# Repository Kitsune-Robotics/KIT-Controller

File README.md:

# KIT-Controller

Hardware for the KIT Controller

Migrated from https://kitsunehosting.net/gitea/Kenwood/lewis-crawler

# Getting Started

## Clone this repo

```shell
git clone https://github.com/Kitsune-Robotics/KIT-Controller.git --recurse-submodules
```

You will *need* the submodules as all of the boards in `Hardware` have several library dependencies.

`Hardware/BackPlane` Contains the backplane for the system, the backplane connects all other cards together.
`Hardware/KIT_Controller` Is the main processing unit of the system, the core computer where this code (will eventually) live
`Hardware/Dev_Card` Is a development tool, made to be slotted into any slot and connected via probes, solder jumpers and wires to aid in developing/debugging

You can re-initalize/update submodules by using the command

```shell
git submodule update --init --recursive
```

## 3D Models

Some libraries (namely my own `kenwoodfox-kicad-libraries` lib) requires setting a path variable to show some 3d models.

Follow the instructions inside of these libraries folders for how to set these paths.

# Parts

The kit controller and its other boards use the Sullins [EBM15DSEH](https://www.digikey.com/en/products/detail/sullins-connector-solutions/EBM15DSEH/927297) to connect to the backplane.

Its a little expensive, in the future the [WingTAT ED30MEBGFBK ](https://www.lcsc.com/product-detail/Card-Edge-Connectors_WingTAT-ED30MEBGFBK_C5242012.html) is a possible replacement.

## Project Layout

If you want to use this project template for yourself, you can find it [here!](https://github.com/KenwoodFox/Project-Template)

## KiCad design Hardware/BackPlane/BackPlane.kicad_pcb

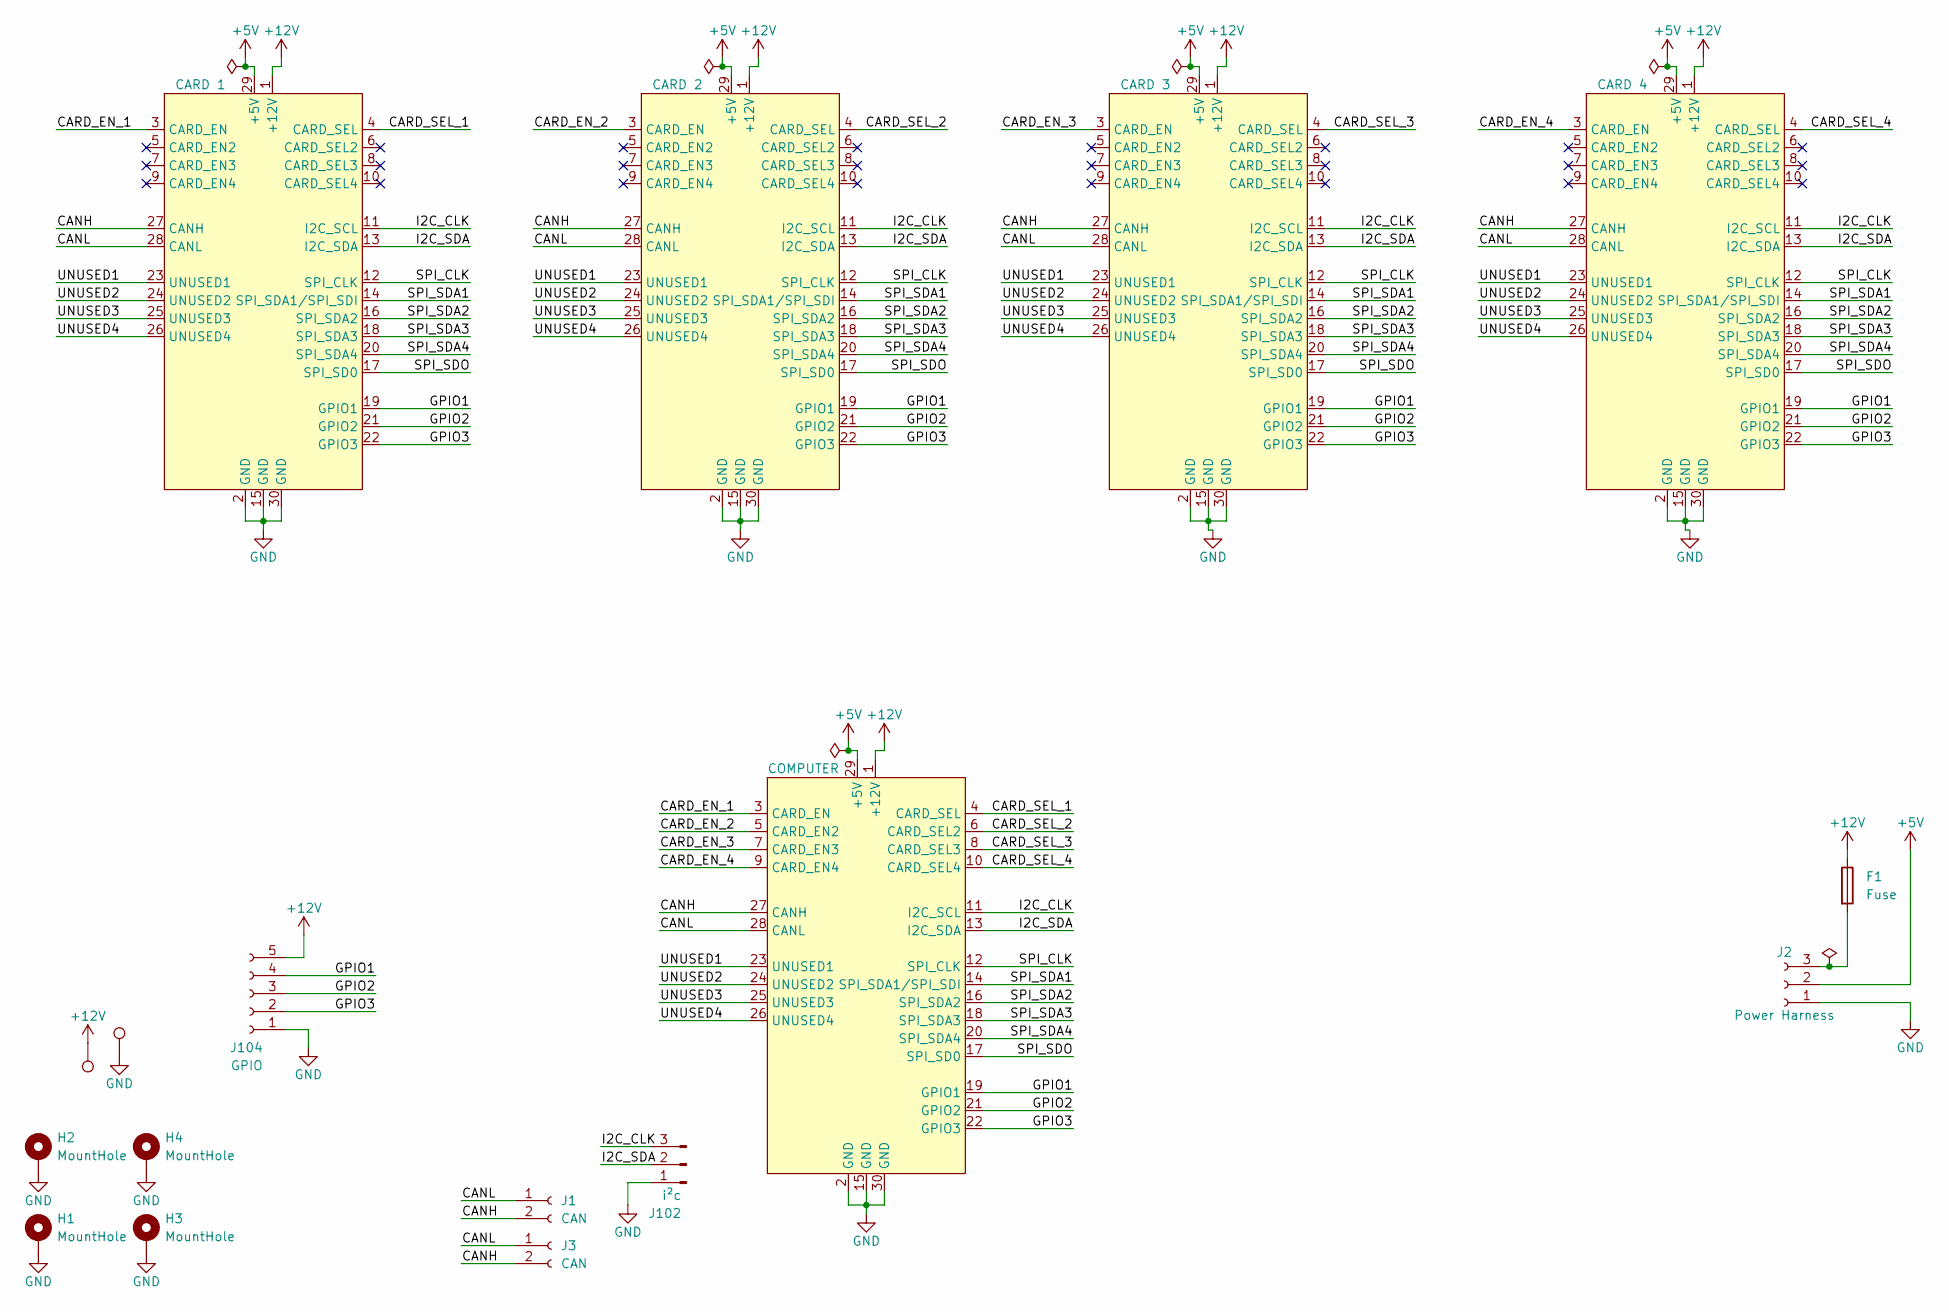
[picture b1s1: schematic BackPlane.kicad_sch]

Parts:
F1: Fuse; Fuseholder_Littelfuse_100_series_5x20mm; LCSC# C3130
H1, H2, H3, H4: MountHole; MountingHole_3.5mm_Pad
J1, J3: CAN; SolderWire-0.5sqmm_1x02_P4.6mm_D0.9mm_OD2.1mm_Relief
J2: Power Harness; SolderWire-0.25sqmm_1x03_P4.5mm_D0.65mm_OD2mm_Relief
J102: i²c; SolderWire-0.25sqmm_1x03_P4.5mm_D0.65mm_OD2mm_Relief
J104: GPIO; SolderWire-0.5sqmm_1x05_P4.6mm_D0.9mm_OD2.1mm_Relief
TP101, TP102: TestPoint; TestPoint_Loop_D2.54mm_Drill1.5mm_Beaded
U101: COMPUTER; EBM15DSEH
U102: CARD 1; EBM15DSEH
U103: CARD 2; EBM15DSEH
U104: CARD 3; EBM15DSEH
U105: CARD 4; EBM15DSEH

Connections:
+5V: J2.2, U101.29 (+5V), U102.29 (+5V), U103.29 (+5V), U104.29 (+5V), U105.29 (+5V)
+12V: F1.1, J104.5, TP101.1, U101.1 (+12V), U102.1 (+12V), U103.1 (+12V), U104.1 (+12V), U105.1 (+12V)
/CANH: J1.2, J3.2, U101.27 (CANH), U102.27 (CANH), U103.27 (CANH), U104.27 (CANH), U105.27 (CANH)
/CANL: J1.1, J3.1, U101.28 (CANL), U102.28 (CANL), U103.28 (CANL), U104.28 (CANL), U105.28 (CANL)
/CARD_EN_1: U101.3 (CARD_EN), U102.3 (CARD_EN)
/CARD_EN_2: U101.5 (CARD_EN2), U103.3 (CARD_EN)
/CARD_EN_3: U101.7 (CARD_EN3), U104.3 (CARD_EN)
/CARD_EN_4: U101.9 (CARD_EN4), U105.3 (CARD_EN)
/CARD_SEL_1: U101.4 (CARD_SEL), U102.4 (CARD_SEL)
/CARD_SEL_2: U101.6 (CARD_SEL2), U103.4 (CARD_SEL)
/CARD_SEL_3: U101.8 (CARD_SEL3), U104.4 (CARD_SEL)
/CARD_SEL_4: U101.10 (CARD_SEL4), U105.4 (CARD_SEL)
/GPIO1: J104.4, U101.19 (GPIO1), U102.19 (GPIO1), U103.19 (GPIO1), U104.19 (GPIO1), U105.19 (GPIO1)
/GPIO2: J104.3, U101.21 (GPIO2), U102.21 (GPIO2), U103.21 (GPIO2), U104.21 (GPIO2), U105.21 (GPIO2)
/GPIO3: J104.2, U101.22 (GPIO3), U102.22 (GPIO3), U103.22 (GPIO3), U104.22 (GPIO3), U105.22 (GPIO3)
/I2C_CLK: J102.3, U101.11 (I2C_SCL), U102.11 (I2C_SCL), U103.11 (I2C_SCL), U104.11 (I2C_SCL), U105.11 (I2C_SCL)
/I2C_SDA: J102.2, U101.13 (I2C_SDA), U102.13 (I2C_SDA), U103.13 (I2C_SDA), U104.13 (I2C_SDA), U105.13 (I2C_SDA)
/SPI_CLK: U101.12 (SPI_CLK), U102.12 (SPI_CLK), U103.12 (SPI_CLK), U104.12 (SPI_CLK), U105.12 (SPI_CLK)
/SPI_SDA1: U101.14 (SPI_SDA1/SPI_SDI), U102.14 (SPI_SDA1/SPI_SDI), U103.14 (SPI_SDA1/SPI_SDI), U104.14 (SPI_SDA1/SPI_SDI), U105.14 (SPI_SDA1/SPI_SDI)
/SPI_SDA2: U101.16 (SPI_SDA2), U102.16 (SPI_SDA2), U103.16 (SPI_SDA2), U104.16 (SPI_SDA2), U105.16 (SPI_SDA2)
/SPI_SDA3: U101.18 (SPI_SDA3), U102.18 (SPI_SDA3), U103.18 (SPI_SDA3), U104.18 (SPI_SDA3), U105.18 (SPI_SDA3)
/SPI_SDA4: U101.20 (SPI_SDA4), U102.20 (SPI_SDA4), U103.20 (SPI_SDA4), U104.20 (SPI_SDA4), U105.20 (SPI_SDA4)
/SPI_SDO: U101.17 (SPI_SD0), U102.17 (SPI_SD0), U103.17 (SPI_SD0), U104.17 (SPI_SD0), U105.17 (SPI_SD0)
/UNUSED1: U101.23 (UNUSED1), U102.23 (UNUSED1), U103.23 (UNUSED1), U104.23 (UNUSED1), U105.23 (UNUSED1)
/UNUSED2: U101.24 (UNUSED2), U102.24 (UNUSED2), U103.24 (UNUSED2), U104.24 (UNUSED2), U105.24 (UNUSED2)
/UNUSED3: U101.25 (UNUSED3), U102.25 (UNUSED3), U103.25 (UNUSED3), U104.25 (UNUSED3), U105.25 (UNUSED3)
/UNUSED4: U101.26 (UNUSED4), U102.26 (UNUSED4), U103.26 (UNUSED4), U104.26 (UNUSED4), U105.26 (UNUSED4)
GND: H1.1, H2.1, H3.1, H4.1, J2.1, J102.1, J104.1, TP102.1, U101.2 (GND), U101.15 (GND), U101.30 (GND), U102.2 (GND), U102.15 (GND), U102.30 (GND), U103.2 (GND), U103.15 (GND), U103.30 (GND), U104.2 (GND), U104.15 (GND), U104.30 (GND), U105.2 (GND), U105.15 (GND), U105.30 (GND)
unnamed: F1.2, J2.3

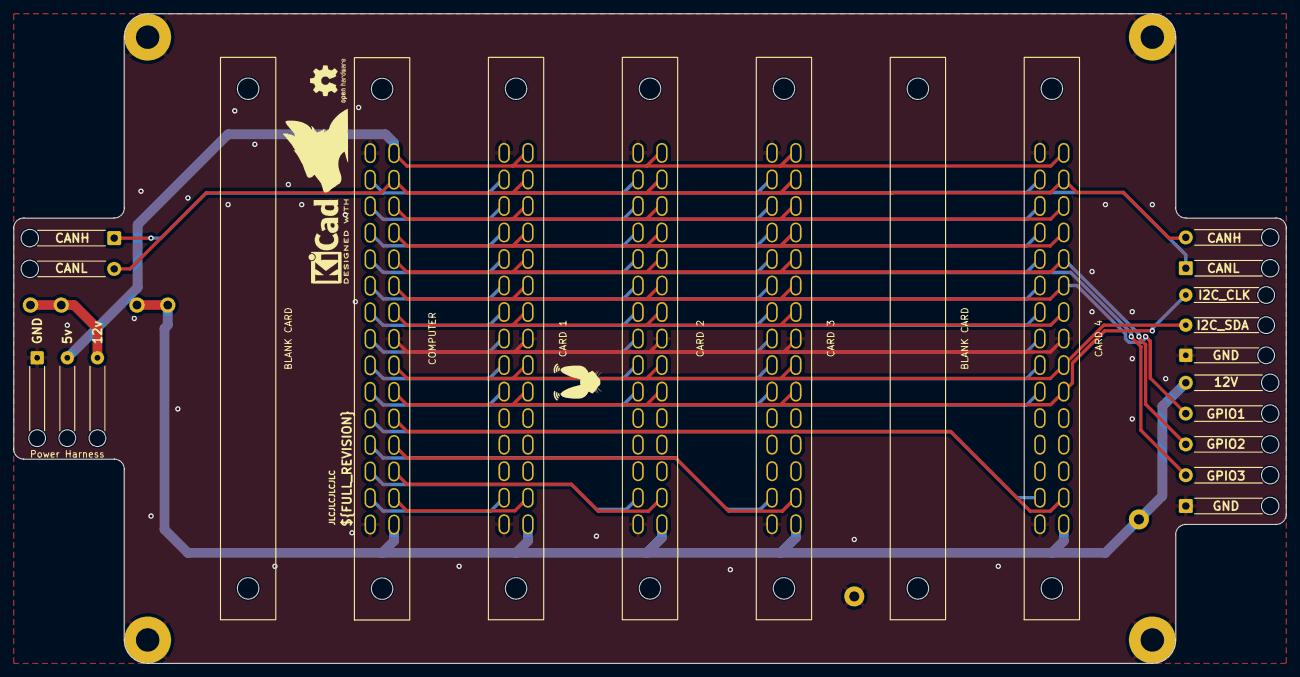
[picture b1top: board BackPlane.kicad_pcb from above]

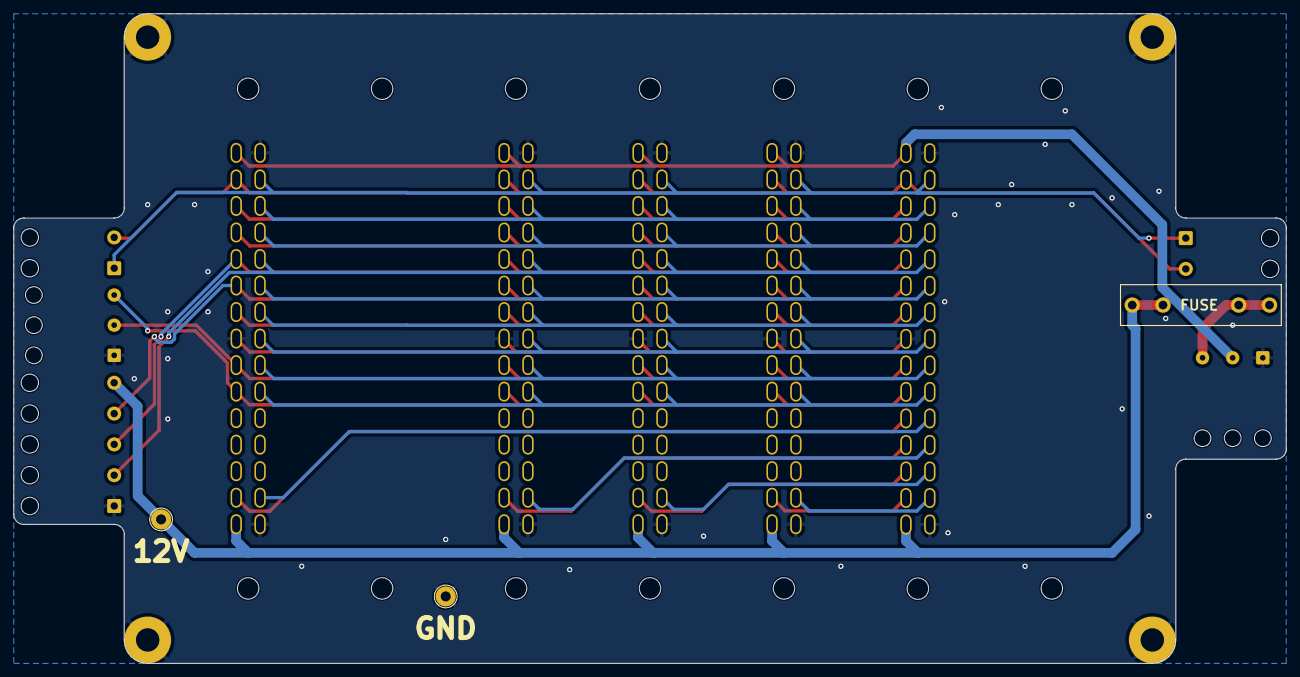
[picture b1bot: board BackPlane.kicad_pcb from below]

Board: 2 copper layers, 190.0 x 97.0 mm, 23 parts (3 on the bottom side), 29 nets.

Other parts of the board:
BLANK1, BLANK2: EBM15DSEH; EBM15DSEH_Blank
LOGO1: LOGO; KITSUNE_LOGO
LOGO2: LOGO; fennec_logo_solid_small
LOGO3: OSHW-Logo2_7.3x6mm_SilkScreen
LOGO5: KiCad-Logo2_5mm_SilkScreen

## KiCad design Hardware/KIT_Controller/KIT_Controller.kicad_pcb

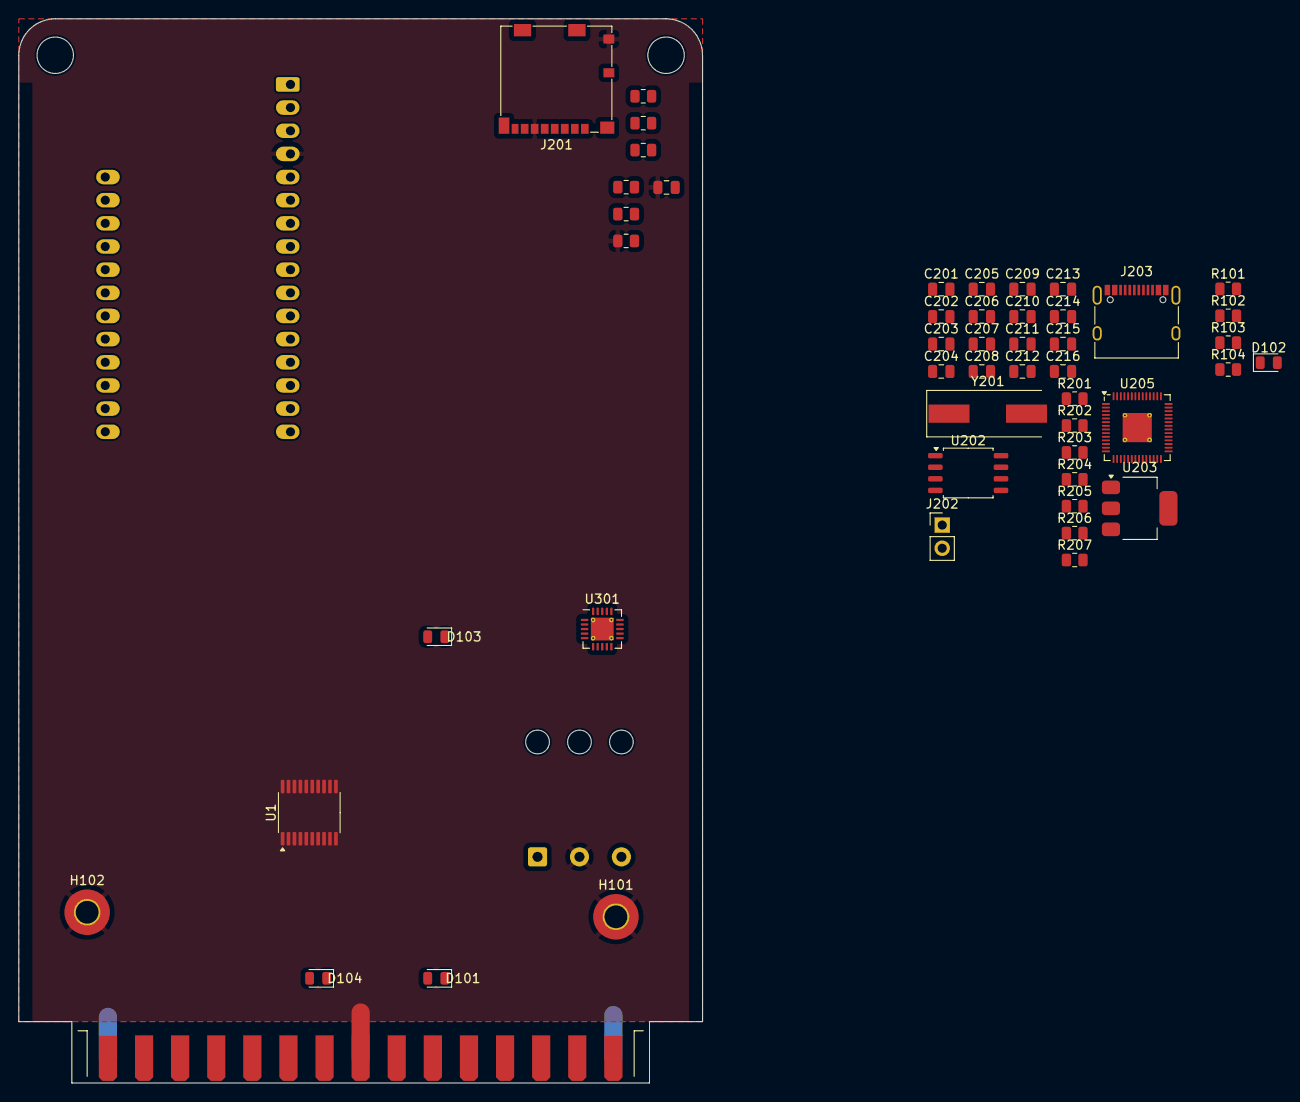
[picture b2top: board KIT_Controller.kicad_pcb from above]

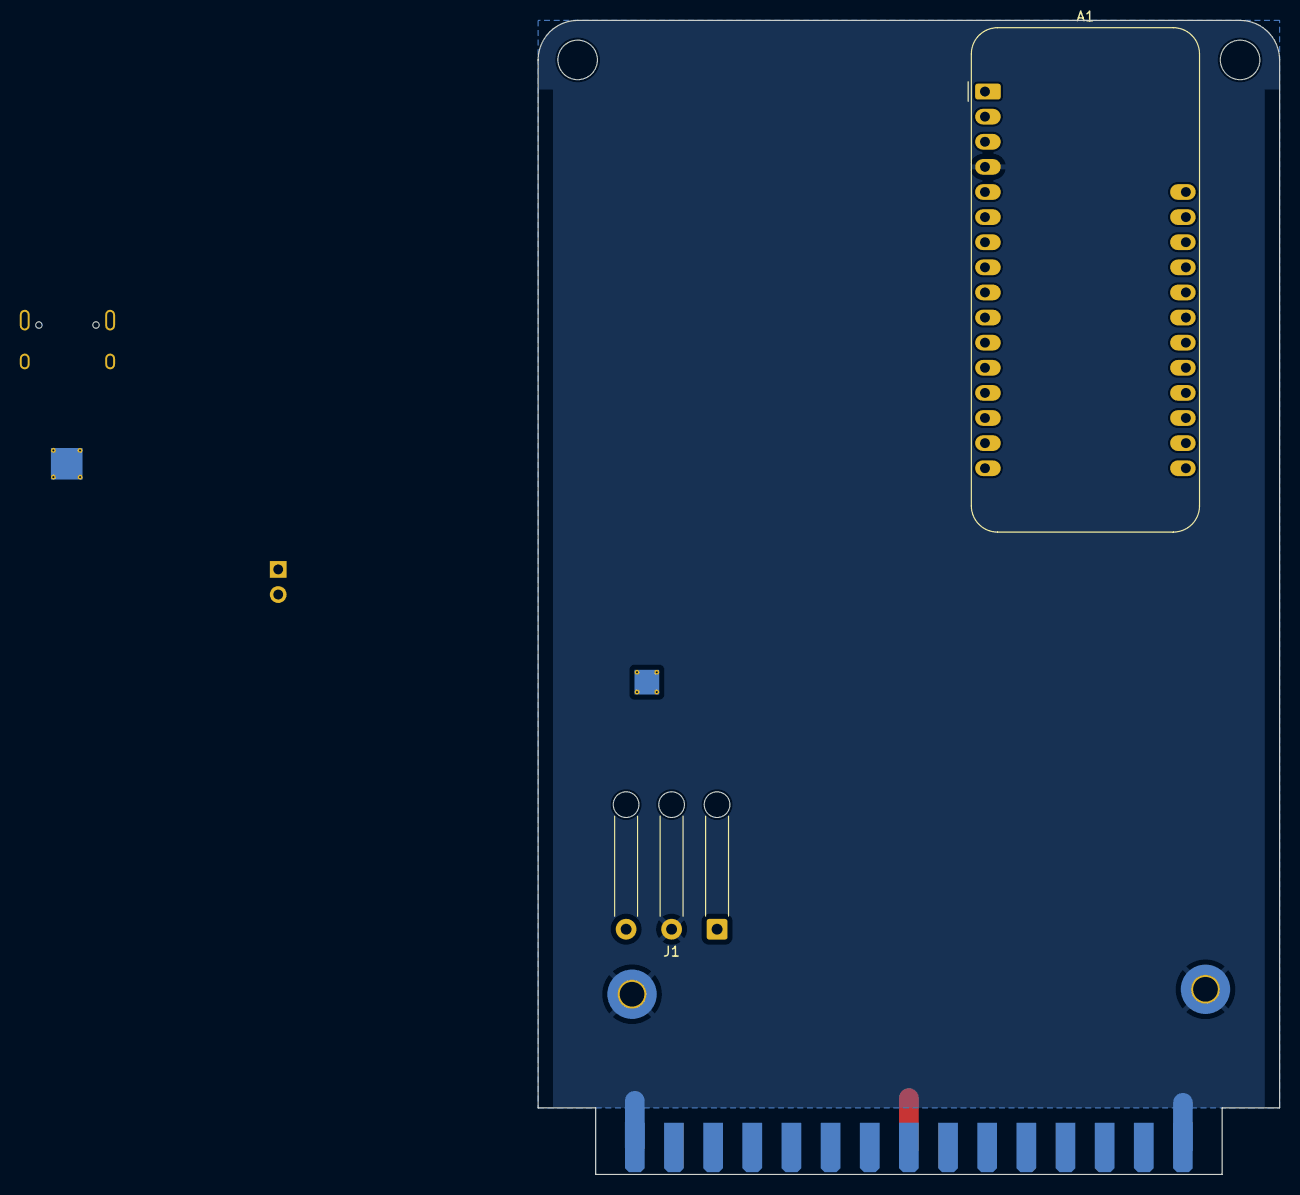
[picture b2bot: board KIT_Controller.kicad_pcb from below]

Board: 2 copper layers, 75.0 x 116.7 mm, 52 parts (2 on the bottom side), 33 nets.

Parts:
A1: Adafruit_Feather_Generic; Adafruit_Feather
C201, C202: 27p; C_0805_2012Metric
C203, C205, C217: 10u; C_0805_2012Metric
C204, C207, C208, C209, C210, C211, C212, C213, C214, C215: 100n; C_0805_2012Metric
C206, C216: 1u; C_0805_2012Metric
D101: BL1; LED_0805_2012Metric
D102: BL2; LED_0805_2012Metric
D103: BL3; LED_0805_2012Metric
D104: BL4; LED_0805_2012Metric
H101, H102: MountingHole_Pad; MountingHole_2.5mm_Pad_TopBottom
J1: CAN; SolderWire-0.5sqmm_1x03_P4.6mm_D0.9mm_OD2.1mm_Relief
J201: Micro_SD_Card_Det1; microSD_HC_Molex_104031-0811
J202: USB_BOOT; PinHeader_1x02_P2.54mm_Vertical
J203: USBC; USB_C_Receptacle_XKB_U262-16XN-4BVC11
R101, R102, R103, R104: 450; R_0805_2012Metric
R201, R203: 1k; R_0805_2012Metric
R202, R215, R216, R217: DNP; R_0805_2012Metric
R204, R205: 27; R_0805_2012Metric
R206, R207: 5K1; R_0805_2012Metric
R208, R209: 10K; R_0805_2012Metric
R210: DNF; R_0805_2012Metric
U1: TXB0108PW; TSSOP-20_4.4x6.5mm_P0.65mm
U102: CARD ?; Lewis_Card_Connector
U202: W25Q128JVS; SOIC-8_5.23x5.23mm_P1.27mm
U203: NCP1117-3.3_SOT223; SOT-223-3_TabPin2
U205: RP2040; QFN-56-1EP_7x7mm_P0.4mm_EP3.2x3.2mm_ThermalVias
U301: CC1101; QFN-20-1EP_4x4mm_P0.5mm_EP2.5x2.5mm_ThermalVias
Y201: Crystal; Crystal_SMD_HC49-SD

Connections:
+1V1: C206.2, C207.2, C208.2, U205.23 (DVDD), U205.45 (VREG_VOUT), U205.50 (DVDD)
+3.3V: C205.2, U203.2 (VO)
+3V3: A1.2 (3V3), C204.2, C209.2, C210.2, C211.2, C212.2, C213.2, C214.2, C215.2, C216.2, C217.2, D101.1 (K), D102.1 (K), D103.1 (K), D104.1 (K), J201.4 (VDD), R202.2, R208.2, R209.2, R215.2, R216.2, R217.2, U202.8 (VCC), U205.1 (IOVDD), U205.10 (IOVDD), U205.22 (IOVDD), U205.33 (IOVDD), U205.42 (IOVDD), U205.43 (ADC_AVDD), U205.44 (VREG_IN), U205.48 (USB_VDD), U205.49 (IOVDD)
/CANH: J1.3, U102.27 (CANH)
/CANL: J1.1, U102.28 (CANL)
/MCU/QSPI_SCLK: U202.6 (CLK), U205.52 (QSPI_SCLK)
/MCU/QSPI_SD0: U202.5 (DI(IO0)), U205.53 (QSPI_SD0)
/MCU/QSPI_SD1: U202.2 (DO(IO1)), U205.55 (QSPI_SD1)
/MCU/QSPI_SD2: U202.3 (IO2), U205.54 (QSPI_SD2)
/MCU/QSPI_SD3: U202.7 (IO3), U205.51 (QSPI_SD3)
/MCU/QSPI_SS: R201.2, R202.1, U202.1 (~CS), U205.56 (QSPI_SS)
/MCU/SD_CLK: J201.5 (CLK), R210.2, R217.1, U205.8 (GPIO6)
/MCU/SD_CMD: J201.3 (CMD), U205.31 (GPIO20)
/MCU/SD_DAT0: J201.7 (DAT0), R216.1, U205.32 (GPIO21)
/MCU/SD_DAT1: J201.8 (DAT1), R208.1, U205.34 (GPIO22)
/MCU/SD_DAT2: J201.1 (DAT2), R209.1, U205.35 (GPIO23)
/MCU/SD_DAT3: J201.2 (DAT3/CD), R215.1, U205.36 (GPIO24)
/MCU/USB+: J203.A6 (D+), J203.B6 (D+)
/MCU/USB-: J203.A7 (D-), J203.B7 (D-)
/MCU/XIN: C201.2, U205.20 (XIN), Y201.2
/MCU/XOUT: R203.2, U205.21 (XOUT)
GND: A1.4 (GND), C201.1, C202.1, C203.1, C204.1, C205.1, C206.1, C207.1, C208.1, C209.1, C210.1, C211.1, C212.1, C213.1, C214.1, C215.1, C216.1, C217.1, H101.1, H102.1, J1.2, J201.6 (VSS), J201.10 (SHIELD), J202.2, J203.A1 (GND), J203.A12 (GND), J203.B1 (GND), J203.B12 (GND), J203.S1 (SHIELD), R101.1, R102.1, R103.1, R104.1, R206.1, R207.1, R210.1, U102.2 (GND), U102.15 (GND), U102.30 (GND), U202.4 (GND), U203.1 (GND), U205.19 (TESTEN), U205.57 (GND)
unnamed: C202.2, R203.1, Y201.1
unnamed: D101.2 (A), R101.2
unnamed: D102.2 (A), R102.2
unnamed: D103.2 (A), R103.2
unnamed: D104.2 (A), R104.2
unnamed: J202.1, R201.1
unnamed: J203.A5 (CC1), R207.2
unnamed: J203.B5 (CC2), R206.2
unnamed: R205.1, U205.46 (USB_DM)
unnamed: R204.1, U205.47 (USB_DP)
VBUS: C203.2, J203.A4 (VBUS), J203.A9 (VBUS), J203.B4 (VBUS), J203.B9 (VBUS), U203.3 (VI)

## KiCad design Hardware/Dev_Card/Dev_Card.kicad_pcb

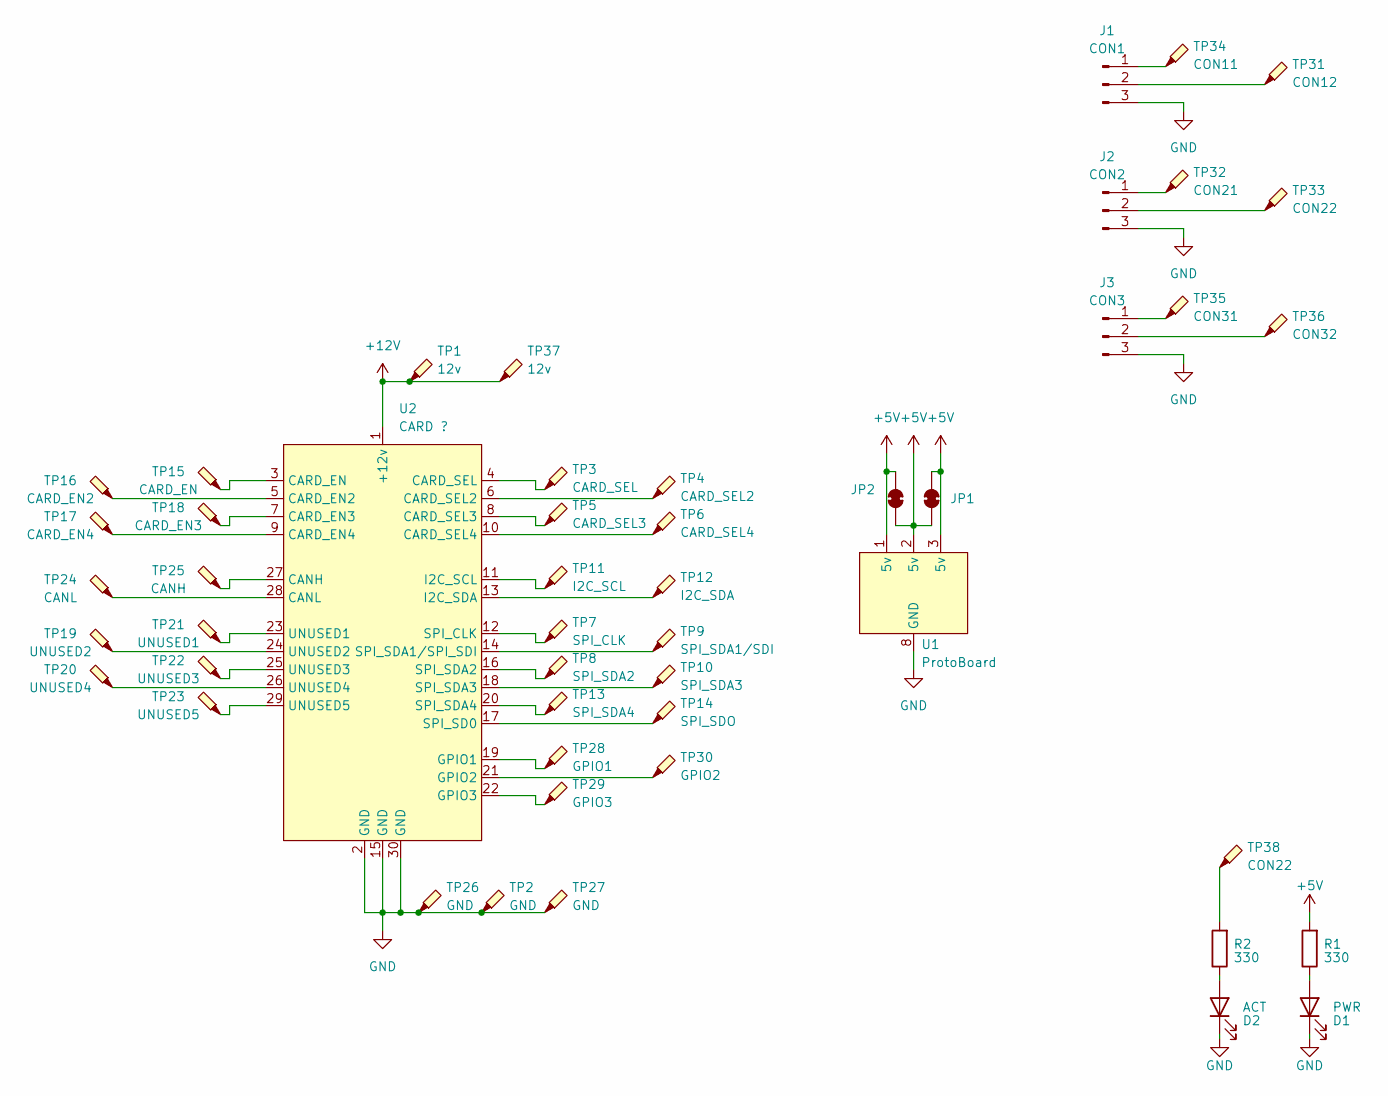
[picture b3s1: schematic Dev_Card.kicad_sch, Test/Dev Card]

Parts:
D1: PWR; LED_D3.0mm_Horizontal_O1.27mm_Z2.0mm
D2: ACT; LED_D3.0mm_Horizontal_O1.27mm_Z2.0mm
J1: CON1; JST_XH_S3B-XH-A-1_1x03_P2.50mm_Horizontal
J2: CON2; JST_XH_S3B-XH-A-1_1x03_P2.50mm_Horizontal
J3: CON3; JST_XH_S3B-XH-A-1_1x03_P2.50mm_Horizontal
JP1, JP2: SolderJumper_2_Bridged; SolderJumper-2_P1.3mm_Bridged_Pad1.0x1.5mm
R1, R2: 330; R_0805_2012Metric
TP1, TP37: 12v; TestPoint_Bridge_Pitch2.54mm_Drill1.0mm
TP2, TP26, TP27: GND; TestPoint_Bridge_Pitch2.54mm_Drill1.0mm
TP3: CARD_SEL; TestPoint_Bridge_Pitch2.54mm_Drill1.0mm
TP4: CARD_SEL2; TestPoint_Bridge_Pitch2.54mm_Drill1.0mm
TP5: CARD_SEL3; TestPoint_Bridge_Pitch2.54mm_Drill1.0mm
TP6: CARD_SEL4; TestPoint_Bridge_Pitch2.54mm_Drill1.0mm
TP7: SPI_CLK; TestPoint_Bridge_Pitch2.54mm_Drill1.0mm
TP8: SPI_SDA2; TestPoint_Bridge_Pitch2.54mm_Drill1.0mm
TP9: SPI_SDA1/SDI; TestPoint_Bridge_Pitch2.54mm_Drill1.0mm
TP10: SPI_SDA3; TestPoint_Bridge_Pitch2.54mm_Drill1.0mm
TP11: I2C_SCL; TestPoint_Bridge_Pitch2.54mm_Drill1.0mm
TP12: I2C_SDA; TestPoint_Bridge_Pitch2.54mm_Drill1.0mm
TP13: SPI_SDA4; TestPoint_Bridge_Pitch2.54mm_Drill1.0mm
TP14: SPI_SDO; TestPoint_Bridge_Pitch2.54mm_Drill1.0mm
TP15: CARD_EN; TestPoint_Bridge_Pitch2.54mm_Drill1.0mm
TP16: CARD_EN2; TestPoint_Bridge_Pitch2.54mm_Drill1.0mm
TP17: CARD_EN4; TestPoint_Bridge_Pitch2.54mm_Drill1.0mm
TP18: CARD_EN3; TestPoint_Bridge_Pitch2.54mm_Drill1.0mm
TP19: UNUSED2; TestPoint_Bridge_Pitch2.54mm_Drill1.0mm
TP20: UNUSED4; TestPoint_Bridge_Pitch2.54mm_Drill1.0mm
TP21: UNUSED1; TestPoint_Bridge_Pitch2.54mm_Drill1.0mm
TP22: UNUSED3; TestPoint_Bridge_Pitch2.54mm_Drill1.0mm
TP23: UNUSED5; TestPoint_Bridge_Pitch2.54mm_Drill1.0mm
TP24: CANL; TestPoint_Bridge_Pitch2.54mm_Drill1.0mm
TP25: CANH; TestPoint_Bridge_Pitch2.54mm_Drill1.0mm
TP28: GPIO1; TestPoint_Bridge_Pitch2.54mm_Drill1.0mm
TP29: GPIO3; TestPoint_Bridge_Pitch2.54mm_Drill1.0mm
TP30: GPIO2; TestPoint_Bridge_Pitch2.54mm_Drill1.0mm
TP31: CON12; TestPoint_Bridge_Pitch2.54mm_Drill1.0mm
TP32: CON21; TestPoint_Bridge_Pitch2.54mm_Drill1.0mm
TP33, TP38: CON22; TestPoint_Bridge_Pitch2.54mm_Drill1.0mm
TP34: CON11; TestPoint_Bridge_Pitch2.54mm_Drill1.0mm
TP35: CON31; TestPoint_Bridge_Pitch2.54mm_Drill1.0mm
TP36: CON32; TestPoint_Bridge_Pitch2.54mm_Drill1.0mm
U1: ProtoBoard; ProtoBoardLayout
U2: CARD ?; Lewis_Card_Connector

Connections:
+5V: JP1.1 (A), JP1.2 (B), JP2.1 (A), JP2.2 (B), R1.2, U1.1 (5v), U1.2 (5v), U1.3 (5v)
+12V: TP1.1, TP37.1, U2.1 (+12v)
GND: D1.1 (K), D2.1 (K), J1.3, J2.3, J3.3, TP2.1, TP26.1, TP27.1, U1.8 (GND), U2.2 (GND), U2.15 (GND), U2.30 (GND)
unnamed: D1.2 (A), R1.1
unnamed: D2.2 (A), R2.1
unnamed: J1.1, TP34.1
unnamed: J1.2, TP31.1
unnamed: J2.1, TP32.1
unnamed: J2.2, TP33.1
unnamed: J3.1, TP35.1
unnamed: J3.2, TP36.1
unnamed: R2.2, TP38.1
unnamed: TP25.1, U2.27 (CANH)
unnamed: TP24.1, U2.28 (CANL)
unnamed: TP16.1, U2.5 (CARD_EN2)
unnamed: TP18.1, U2.7 (CARD_EN3)
unnamed: TP17.1, U2.9 (CARD_EN4)
unnamed: TP15.1, U2.3 (CARD_EN)
unnamed: TP4.1, U2.6 (CARD_SEL2)
unnamed: TP5.1, U2.8 (CARD_SEL3)
unnamed: TP6.1, U2.10 (CARD_SEL4)
unnamed: TP3.1, U2.4 (CARD_SEL)
unnamed: TP28.1, U2.19 (GPIO1)
unnamed: TP30.1, U2.21 (GPIO2)
unnamed: TP29.1, U2.22 (GPIO3)
unnamed: TP11.1, U2.11 (I2C_SCL)
unnamed: TP12.1, U2.13 (I2C_SDA)
unnamed: TP7.1, U2.12 (SPI_CLK)
unnamed: TP14.1, U2.17 (SPI_SD0)
unnamed: TP9.1, U2.14 (SPI_SDA1/SPI_SDI)
unnamed: TP8.1, U2.16 (SPI_SDA2)
unnamed: TP10.1, U2.18 (SPI_SDA3)
unnamed: TP13.1, U2.20 (SPI_SDA4)
unnamed: TP21.1, U2.23 (UNUSED1)
unnamed: TP19.1, U2.24 (UNUSED2)
unnamed: TP22.1, U2.25 (UNUSED3)
unnamed: TP20.1, U2.26 (UNUSED4)
unnamed: TP23.1, U2.29 (UNUSED5)

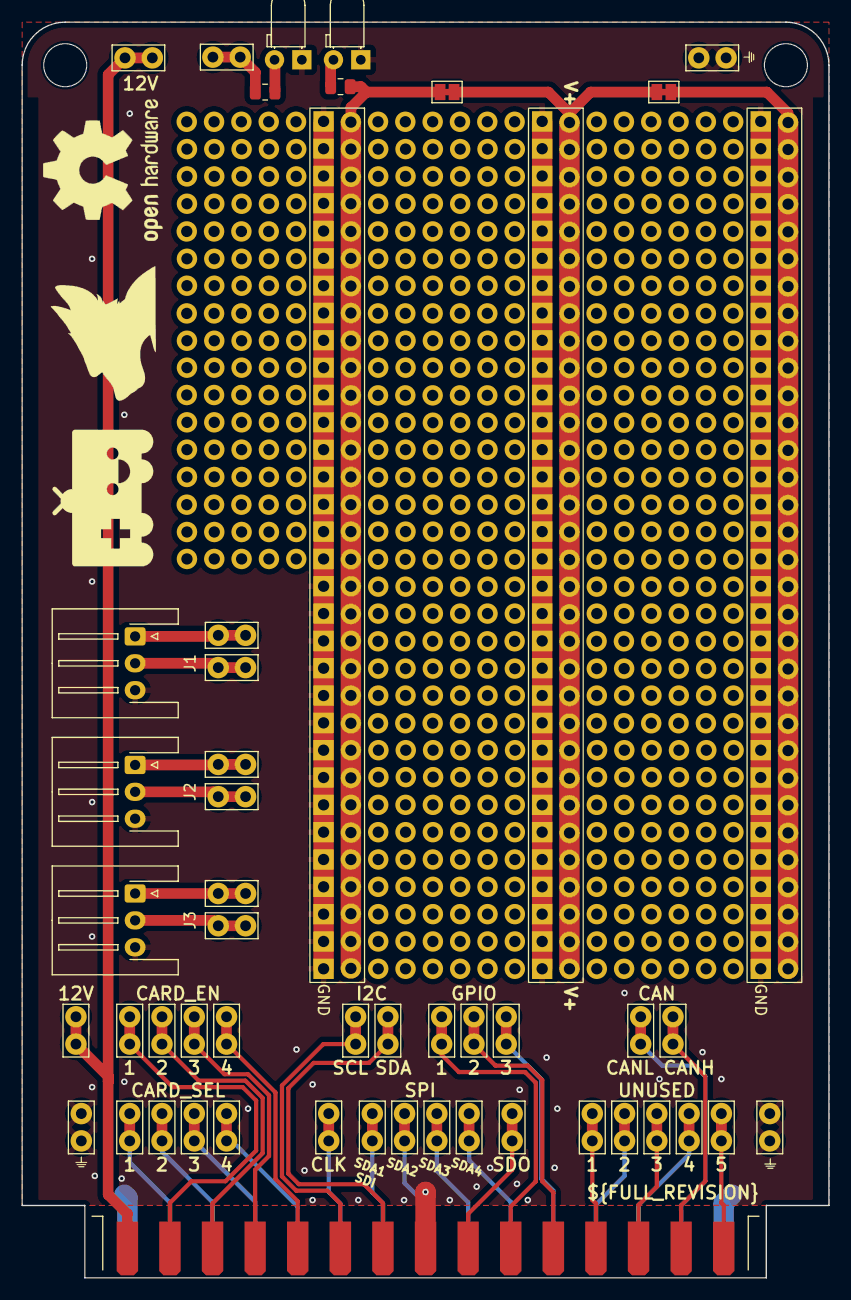
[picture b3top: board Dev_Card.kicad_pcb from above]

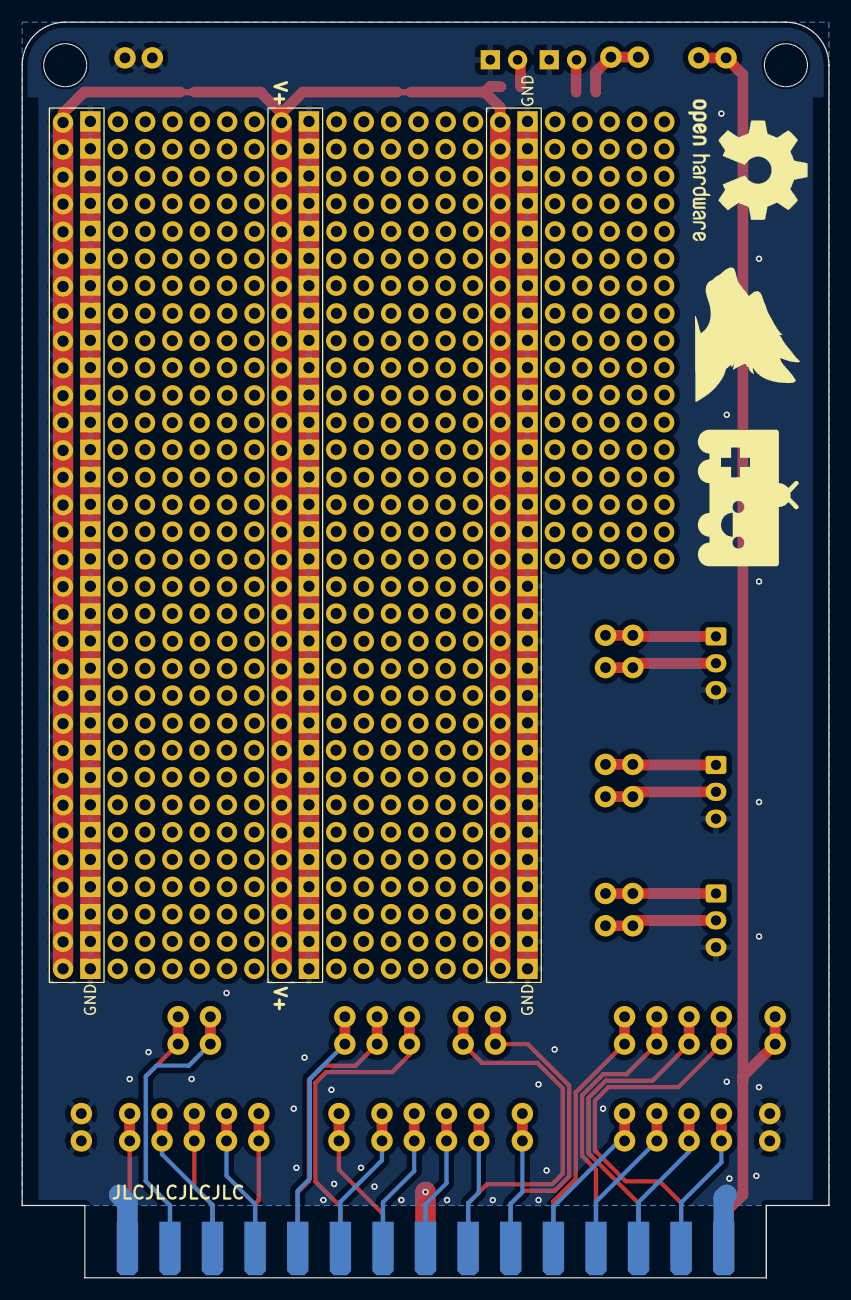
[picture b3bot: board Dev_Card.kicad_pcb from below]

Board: 2 copper layers, 75.0 x 116.7 mm, 55 parts (3 on the bottom side), 38 nets.

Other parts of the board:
LOGO1, LOGO1#2: LOGO; ROBOTSTREAMER_LOGO
LOGO2, LOGO2#2: LOGO; KITSUNE_LOGO
LOGO3, LOGO3#2: OSHW-Logo2_14.6x12mm_SilkScreen

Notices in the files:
parts and their libraries:
Copyright 2021 Accelerated Designs. All rights reserved.
